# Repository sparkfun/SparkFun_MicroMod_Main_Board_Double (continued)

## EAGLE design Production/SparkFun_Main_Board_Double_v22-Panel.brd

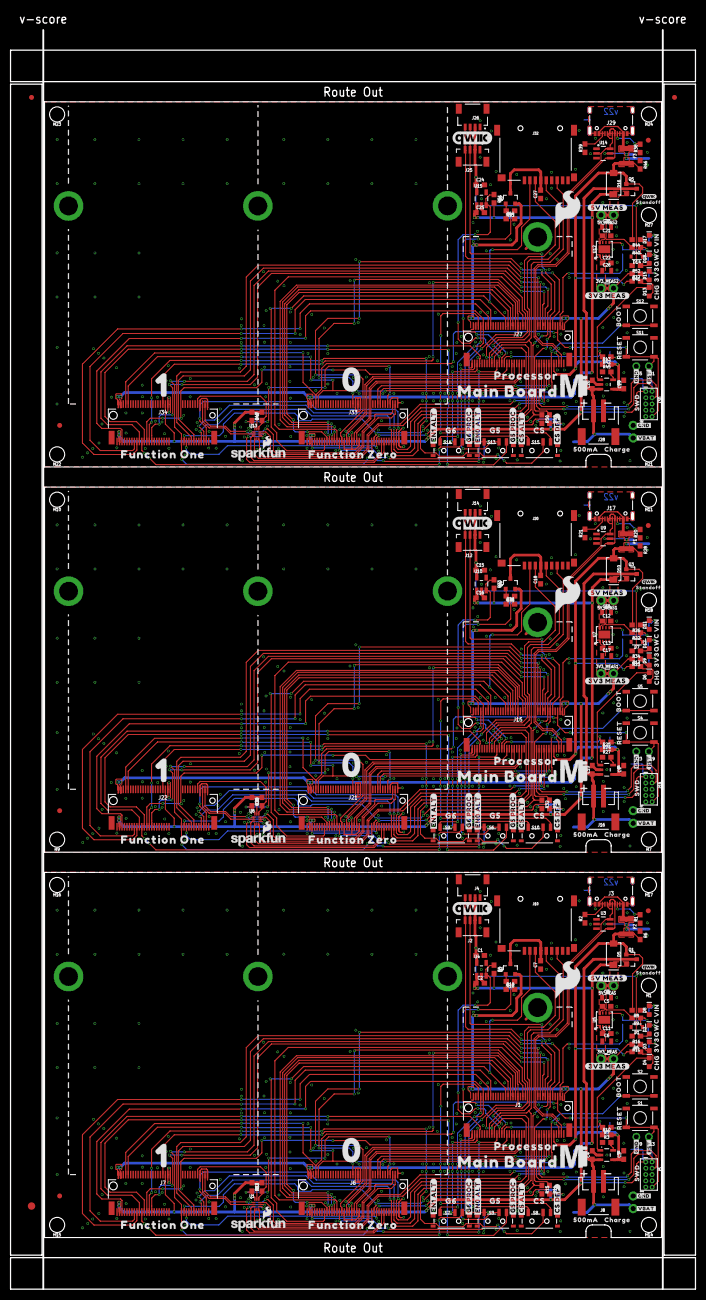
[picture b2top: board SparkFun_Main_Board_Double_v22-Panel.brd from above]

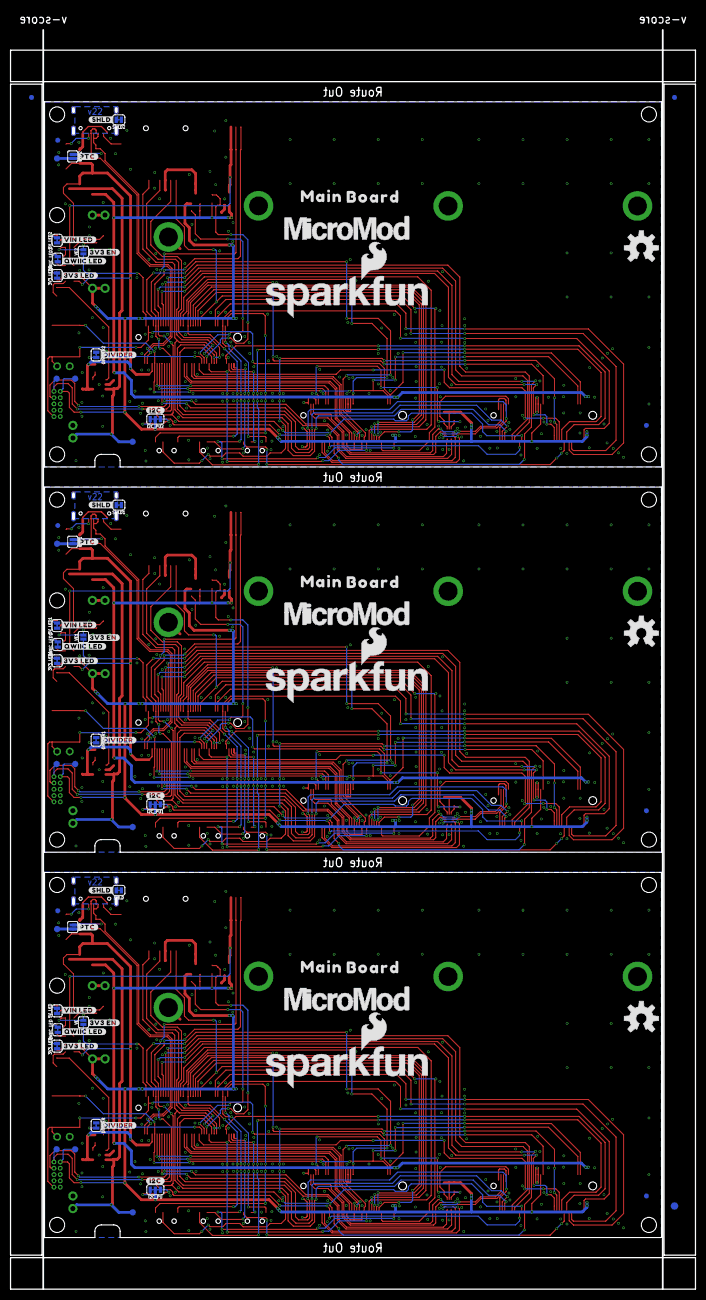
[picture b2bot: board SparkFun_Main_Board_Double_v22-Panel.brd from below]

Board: 2 copper layers, 138.2 x 254.0 mm, 408 parts (84 on the bottom side), 252 nets.

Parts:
3V3_LED, 3V3_LED1, 3V3_LED2, 5V_LED, 5V_LED1, 5V_LED2: JUMPER-SMT_2_NC_TRACE_SILK; SMT-JUMPER_2_NC_TRACE_SILK
3V3_MEAS, 3V3_MEAS1, 3V3_MEAS2, 5V_MEAS, 5V_MEAS1, 5V_MEAS2: JUMPER-COMBO_2_NC_TRACE; COMBO-JUMPER_2_NC_TRACE
BYP, BYP1, BYP2: JUMPER-SMT_2_NO_SILK; SMT-JUMPER_2_NO_SILK
C1, C2, C15, C16, C24, C25: 1.0uF; 0603
C3, C4, C9, C10, C11, C13, C19, C20, C22: 4.7uF; 0603
C5, C12, C21: 0.1uF; 0603
C6, C8, C14, C17, C23, C26: 10uF; 0805
C7, C18, C27: 10uF; 0603
D1, D7, D14: 3.3V; SOD-323
D2, D3, D8, D9, D11, D12, D15, D17, D18: RED; LED-0603
D4, D6, D13: Yellow; LED-0603
D5, D10, D16: 3A/40V/500mV; SMA-DIODE
DIVIDER, DIVIDER1, DIVIDER2: JUMPER-SMT_2_NC_TRACE_SILK; SMT-JUMPER_2_NC_TRACE_SILK
E$1, E$2, E$3, E$4: FIDUCIAL-1X2
E$5, E$6: FIDUCIAL-1.5X3
F1, F2, F3: 6V/2A; 1210
FD1, FD2, FD3, FD4, FD5, FD6, FD7, FD8, FD9, FD10, FD11, FD12: FIDUCIAL1X2; FIDUCIAL-1X2
H1, H7, H9, H10, H11, H14, H15, H16, H17, H18, H21, H22, H23, H24, H27: STAND-OFFTIGHT; STAND-OFF-TIGHT
H2, H3, H4, H5, H6, H8, H12, H13, H19, H20, H25, H26: STAND-OFF-REFLOW-M2.5_2.5MM_TALL; STAND-OFF-REFLOW-M2.5
I2C_PU, I2C_PU1, I2C_PU2: JUMPER-SMT_3_2-NC_TRACE_SILK; SMT-JUMPER_3_2-NC_TRACE_SILK
J1, J15, J27: MICROMOD-2222-C; M.2-CONNECTOR-E
J2, J12, J25: Vertical Qwiic Connector; JST04_1MM_VERT
J3, J17, J29: USB-C-16P-2LAYER-PADS
J4, J14, J26: QWIIC_RIGHT_ANGLE; JST04_1MM_RA
J5, J18, J30: CORTEX_JTAG_DEBUG_MINIMUM_PTH; 2X5-PTH-1.27MM
J6, J7, J21, J22, J33, J34: MICROMOD_FUNCTION_MAIN; M.2-CONNECTOR-E-FUNCTION-STANDARD
J8, J16, J28: JST-2-SMD
J9, J13, J19, J23, J31, J35: 1X01_NO_SILK
J10, J20, J32: MICRO-SD-PUSH-PUSH-EXT-PIN; MICROSD-EXTERNALPIN
J11, J24, J36: 1X02_NO_SILK
LOGO1, LOGO4, LOGO7: QWIIC_LOGO_8MM; QWIIC_8MM
LOGO2, LOGO5, LOGO8: SFE_LOGO_NAME_FLAME.3_INCH; SFE_LOGO_NAME_FLAME_.3
LOGO3, LOGO6, LOGO9: OSHW-LOGOL; OSHW-LOGO-L
Q1, Q3, Q5: 3.1A/30V/105mΩ; SOT23-3
Q2, Q4, Q6: 20V/4.2A/52mΩ/1.4W; SOT23-3
QWIIC_LED, QWIIC_LED1, QWIIC_LED2: JUMPER-SMT_2_NC_TRACE_SILK; SMT-JUMPER_2_NC_TRACE_SILK
R1, R2, R20, R21, R38, R39: 5.1k; 0603
R3, R27, R45: 2.0k; 0603
R4, R9, R12, R13, R19, R22, R29, R30, R33, R36, R40, R47, R48, R51, R54: 100k; 0603
R5, R17, R37: 4.7k; 0603
R6, R7, R24, R28, R42, R46: 10k; 0603
R8, R14, R15, R26, R31, R32, R44, R49, R50: 2.2k; 0603
R10, R25, R43: 20k; 0603
R11, R16, R23, R34, R41, R52: 1k; 0603
R18, R35, R53: 100; 0603
S1, S4, S11: Reset; TACTILE_SWITCH_SMD_5.2MM
S2, S5, S12: BOOT; TACTILE_SWITCH_SMD_5.2MM
S3, S6, S7, S8, S9, S10, S13, S14, S15: SWITCH_SPST_SMD_A
SHLD, SHLD1, SHLD2: JUMPER-SMT_2_NC_TRACE_SILK; SMT-JUMPER_2_NC_TRACE_SILK
TP1, TP2, TP3, TP4, TP5, TP6, TP7, TP8, TP9, TP10, TP11, TP12: TEST-POINT3X5; PAD.03X.05
U1, U8, U13: STG3856QTR; STG3856
U2, U6, U11: MCP73831; SOT23-5
U3, U9, U14: ESD Diode; SOT-23-6
U4, U10, U15: AP7347DQ-33W5-7K-3.3V; SOT25
U5, U7, U12: AP7361C-33; UDFN-8
U$1, U$82, U$128: #3V3_LED#22
U$2, U$81, U$127: #3V3_EN#23
U$3, U$89, U$135: ##RST##8
U$4, U$47, U$93: 3V332533
U$5, U$48, U$94: VIN32532
U$6, U$49, U$95: CHG32531
U$7, U$72, U$118: #SHLD#501
U$8, U$50, U$96: BOOT32541
U$9, U$51, U$97: RESET32540
U$10, U$52, U$98: PROCESSOR525
U$11, U$53, U$99: FUNCTION_ZERO520
U$12, U$54, U$100: FUNCTION_ONE524
U$13, U$58, U$104: MAIN523
U$14, U$55, U$101: MICROMOD_MI_LOGO_1
U$15, U$56, U$102: 0523
U$16, U$57, U$103: 1524
U$17, U$61, U$107: MICROMOD_LOGO_1
U$18, U$59, U$105: BOARD524
U$19, U$77, U$123: G518
U$20, U$65, U$111: #CS_ALT#20
U$21, U$60, U$106: MAIN_BOARD5523
U$22, U$62, U$108: QWIIC_3MM
U$23, U$63, U$109: STANDOFF501
U$24, U$64, U$110: SFE_LOGO_FLAME_.3
U$25, U$80, U$126: SWD6522
U$26, U$74, U$120: #3V3_MEAS#6522
U$27, U$71, U$117: CHARGE501
U$28, U$83, U$129: #QWIIC_LED#22
U$29, U$78, U$124: G6519
U$30, U$73, U$119: #I2C#501
U$31, U$75, U$121: #5V_MEAS#6522
U$32, U$79, U$125: CS17
U$33, U$76, U$122: 500MA6520
U$34, U$66, U$112: #CS_DEF#19
U$35, U$67, U$113: #G5_PROC#21
U$36, U$68, U$114: #G6_PROC#21
U$37, U$69, U$115: #EN0_ALT#21
U$38, U$70, U$116: #EN1_ALT#21
U$39, U$40, U$90, U$91, U$136, U$137: #GND#10
U$41, U$84, U$130: #DIVIDER#23
U$42, U$85, U$131: #VIN_LED#24
U$43, U$86, U$132: QWC18
U$44, U$87, U$133: SFE_LOGO_NAME_FLAME_.1
U$45, U$88, U$134: #PTC#13
U$46, U$92, U$138: #VBAT#9
VE, VE1, VE2: JUMPER-SMT_2_NO_SILK; SMT-JUMPER_2_NO_SILK

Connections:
3.3V: 3V3_MEAS.2, 3V3_MEAS.4, I2C_PU.2, J1.2, J1.74, J5.1, J6.73, J7.36, J7.73, Q2.2, R11.2, R12.2, R13.1, TP2.1, U1.P11
3.3V1: 3V3_MEAS1.2, 3V3_MEAS1.4, I2C_PU1.2, J15.2, J15.74, J18.1, J21.73, J22.36, J22.73, Q4.2, R23.2, R29.2, R30.1, TP5.1, U8.P11
3.3V2: 3V3_MEAS2.2, 3V3_MEAS2.4, I2C_PU2.2, J27.2, J27.74, J30.1, J33.73, J34.36, J34.73, Q6.2, R41.2, R47.2, R48.1, TP9.1, U13.P11
3.3V_EN: J1.4, VE.1
3.3V_EN1: J15.4, VE1.1
3.3V_EN2: J27.4, VE2.1
3.3V_EN_VE: D1.C, R9.1, U5.5, VE.2
3.3V_EN_VE1: D7.C, R22.1, U7.5, VE1.2
3.3V_EN_VE2: D14.C, R40.1, U12.5, VE2.2
3.3V_QWIIC: C1.1, J2.2, J4.2, R16.2, U4.5
3.3V_QWIIC1: C15.1, J12.2, J14.2, R34.2, U10.5
3.3V_QWIIC2: C24.1, J25.2, J26.2, R52.2, U15.5
3V3_MEAS: 3V3_MEAS.1, 3V3_MEAS.3, C6.1, C11.1, U5.1
3V3_MEAS1: 3V3_MEAS1.1, 3V3_MEAS1.3, C13.1, C17.1, U7.1
3V3_MEAS2: 3V3_MEAS2.1, 3V3_MEAS2.3, C22.1, C26.1, U12.1
5V_MEAS: 5V_MEAS.2, 5V_MEAS.4, C5.1, C8.1, R9.2, U5.8
5V_MEAS1: 5V_MEAS1.2, 5V_MEAS1.4, C12.1, C14.1, R22.2, U7.8
5V_MEAS2: 5V_MEAS2.2, 5V_MEAS2.4, C21.1, C23.1, R40.2, U12.8
!BOOT!: J1.11, J6.66, J7.66, S2.3, S2.4
!BOOT!1: J15.11, J21.66, J22.66, S5.3, S5.4
!BOOT!2: J27.11, J33.66, J34.66, S12.3, S12.4
!CS0!-PROCESSOR: J1.55, J6.49
!CS0!-PROCESSOR1: J15.55, J21.49
!CS0!-PROCESSOR2: J27.55, J33.49
!CS1!-PROC-JUMPER: J7.49, S8.2
!CS1!-PROC-JUMPER1: J22.49, S10.2
!CS1!-PROC-JUMPER2: J34.49, S15.2
!CS1!-PROCESSOR: J1.70, S8.1
!CS1!-PROCESSOR1: J15.70, S10.1
!CS1!-PROCESSOR2: J27.70, S15.1
!DFU-FC0!: J6.10, R13.2, U1.P12
!DFU-FC0!1: J21.10, R30.2, U8.P12
!DFU-FC0!2: J33.10, R48.2, U13.P12
!DFU-FC1!: J7.10, R12.1, U1.P10
!DFU-FC1!1: J22.10, R29.1, U8.P10
!DFU-FC1!2: J34.10, R47.1, U13.P10
!RESET!: J1.6, J5.10, J6.68, J7.68, J13.1, S1.3, S1.4
!RESET!1: J15.6, J18.10, J19.1, J21.68, J22.68, S4.3, S4.4
!RESET!2: J27.6, J30.10, J31.1, J33.68, J34.68, S11.3, S11.4
A0-PROCESSOR: J1.34, J6.38
A0-PROCESSOR1: J15.34, J21.38
A0-PROCESSOR2: J27.34, J33.38
A1-PROCESSOR/!CS1!-ALT: J1.38, J7.38, S8.3
A1-PROCESSOR/!CS1!-ALT1: J15.38, J22.38, S10.3
A1-PROCESSOR/!CS1!-ALT2: J27.38, J34.38, S15.3
CTS1-PROCESSOR: J1.15, J6.16
CTS1-PROCESSOR1: J15.15, J21.16
CTS1-PROCESSOR2: J27.15, J33.16
D0-PROCESSOR: J1.10, J6.47
D0-PROCESSOR1: J15.10, J21.47
D0-PROCESSOR2: J27.10, J33.47
D1-PROCESSOR: J1.18, J7.47
D1-PROCESSOR1: J15.18, J22.47
D1-PROCESSOR2: J27.18, J34.47
D+: J1.3, J3.A6, J3.B6, U3.6
D+1: J15.3, J17.A6, J17.B6, U9.6
D+2: J27.3, J29.A6, J29.B6, U14.6
D-: J1.5, J3.A7, J3.B7, U3.4
D-1: J15.5, J17.A7, J17.B7, U9.4
D-2: J27.5, J29.A7, J29.B7, U14.4
G0-PROCESSOR: J1.40, J6.53
G0-PROCESSOR1: J15.40, J21.53
G0-PROCESSOR2: J27.40, J33.53
G1-PROCESSOR: J1.42, J6.55
G1-PROCESSOR1: J15.42, J21.55
G1-PROCESSOR2: J27.42, J33.55
G2-PROCESSOR: J1.44, J6.57
G2-PROCESSOR1: J15.44, J21.57
G2-PROCESSOR2: J27.44, J33.57
G3-PROCESSOR: J1.46, J6.59
G3-PROCESSOR1: J15.46, J21.59
G3-PROCESSOR2: J27.46, J33.59
G4-PROCESSOR/SD_CARD_!CS!: J1.48, J6.61, J10.2
G4-PROCESSOR/SD_CARD_!CS!1: J15.48, J20.2, J21.61
G4-PROCESSOR/SD_CARD_!CS!2: J27.48, J32.2, J33.61
G5-JUMPER: J1.73, S3.2
G5-JUMPER1: J15.73, S6.2
G5-JUMPER2: J27.73, S13.2
G5-PROCESSOR: J7.53, S3.1
G5-PROCESSOR1: J22.53, S6.1
G5-PROCESSOR2: J34.53, S13.1
G6-JUMPER: J1.71, S7.2
G6-JUMPER1: J15.71, S9.2
G6-JUMPER2: J27.71, S14.2
G6-PROCESSOR: J7.55, S7.1
G6-PROCESSOR1: J22.55, S9.1
G6-PROCESSOR2: J34.55, S14.1
G7-PROCESSOR: J1.69, J7.57
G7-PROCESSOR1: J15.69, J22.57
G7-PROCESSOR2: J27.69, J34.57
GND: 3V3_LED.1, 5V_LED.1, C1.2, C2.2, C3.2, C4.2, C5.2, C6.2, C7.1, C8.2, C11.2, D1.A, DIVIDER.1, H2.1, H3.1, H4.1, H8.1, J1.1, J1.7, J1.33, J1.36, J1.39, J1.45, J1.75, J2.1, J3.GND, J3.GND2, J4.1, J5.3, J5.5, J5.9, J6.1, J6.2, J6.8, J6.32, J6.33, J6.34, J6.36, J6.39, J6.45, J6.75, J7.1, J7.2, J7.8, J7.32, J7.33, J7.34, J7.39, J7.45, J7.75, J8.1, J9.1, J10.6, J10.10, J10.11, J10.12, J10.13, J11.1, QWIIC_LED.1, R1.1, R2.1, R3.1, R6.1, R19.2, S1.1, S1.2, S2.1, S2.2, SHLD.1, U1.P5, U2.2, U3.2, U4.2, U5.4, U5.EP
GND1: 3V3_LED1.1, 5V_LED1.1, C9.2, C10.2, C12.2, C13.2, C14.2, C15.2, C16.2, C17.2, C18.1, D7.A, DIVIDER1.1, H5.1, H6.1, H12.1, H13.1, J12.1, J14.1, J15.1, J15.7, J15.33, J15.36, J15.39, J15.45, J15.75, J16.1, J17.GND, J17.GND2, J18.3, J18.5, J18.9, J20.6, J20.10, J20.11, J20.12, J20.13, J21.1, J21.2, J21.8, J21.32, J21.33, J21.34, J21.36, J21.39, J21.45, J21.75, J22.1, J22.2, J22.8, J22.32, J22.33, J22.34, J22.39, J22.45, J22.75, J23.1, J24.1, QWIIC_LED1.1, R20.1, R21.1, R27.1, R28.1, R36.2, S4.1, S4.2, S5.1, S5.2, SHLD1.1, U6.2, U7.4, U7.EP, U8.P5, U9.2, U10.2
GND2: 3V3_LED2.1, 5V_LED2.1, C19.2, C20.2, C21.2, C22.2, C23.2, C24.2, C25.2, C26.2, C27.1, D14.A, DIVIDER2.1, H19.1, H20.1, H25.1, H26.1, J25.1, J26.1, J27.1, J27.7, J27.33, J27.36, J27.39, J27.45, J27.75, J28.1, J29.GND, J29.GND2, J30.3, J30.5, J30.9, J32.6, J32.10, J32.11, J32.12, J32.13, J33.1, J33.2, J33.8, J33.32, J33.33, J33.34, J33.36, J33.39, J33.45, J33.75, J34.1, J34.2, J34.8, J34.32, J34.33, J34.34, J34.39, J34.45, J34.75, J35.1, J36.1, QWIIC_LED2.1, R38.1, R39.1, R45.1, R46.1, R54.2, S11.1, S11.2, S12.1, S12.2, SHLD2.1, U11.2, U12.4, U12.EP, U13.P5, U14.2, U15.2
HOST_D+: J1.35, J6.35
HOST_D+1: J15.35, J21.35
HOST_D+2: J27.35, J33.35
HOST_D-: J1.37, J6.37
HOST_D-1: J15.37, J21.37
HOST_D-2: J27.37, J33.37
I2C_!INT!: J1.16, J6.23, J7.23
I2C_!INT!1: J15.16, J21.23, J22.23
I2C_!INT!2: J27.16, J33.23, J34.23
I2C_SCL: J1.14, J2.4, J4.4, J6.21, J7.21, R15.1
I2C_SCL1: J12.4, J14.4, J15.14, J21.21, J22.21, R32.1
I2C_SCL1-PROCESSOR/QWIIC_EN: J1.53, R4.1, U4.3
I2C_SCL1-PROCESSOR/QWIIC_EN1: J15.53, R33.1, U10.3
I2C_SCL1-PROCESSOR/QWIIC_EN2: J27.53, R51.1, U15.3
I2C_SCL2: J25.4, J26.4, J27.14, J33.21, J34.21, R50.1
I2C_SDA: J1.12, J2.3, J4.3, J6.19, J7.19, R14.1
I2C_SDA1: J12.3, J14.3, J15.12, J21.19, J22.19, R31.1
I2C_SDA1-PROCESSOR/!SD_ENABLE!: J1.51, R18.1
I2C_SDA1-PROCESSOR/!SD_ENABLE!1: J15.51, R35.1
I2C_SDA1-PROCESSOR/!SD_ENABLE!2: J27.51, R53.1
I2C_SDA2: J25.3, J26.3, J27.12, J33.19, J34.19, R49.1
unnamed: D4.A, R5.2
unnamed: 5V_LED.2, D8.C
unnamed: D3.A, R11.1
unnamed: J3.B5, R2.2
unnamed: J3.A5, R1.2
unnamed: R3.2, U2.5
unnamed: DIVIDER.2, R7.1
unnamed: D2.C, QWIIC_LED.2
unnamed: D2.A, R16.1
unnamed: 3V3_LED.2, D3.C
unnamed: I2C_PU.3, R14.2
unnamed: D8.A, R8.1
unnamed: I2C_PU.1, R15.2
unnamed: D4.C, U2.1
unnamed: D6.C, U6.1
unnamed: C7.2, J10.4, Q2.3
unnamed: J17.B5, R21.2
unnamed: Q2.1, R18.2, R19.1
unnamed: J17.A5, R20.2
unnamed: D9.A, R23.1
unnamed: D11.A, R26.1
unnamed: 5V_LED1.2, D11.C
unnamed: 3V3_LED1.2, D9.C
unnamed: I2C_PU1.3, R31.2
unnamed: I2C_PU1.1, R32.2
unnamed: R27.2, U6.5
unnamed: DIVIDER1.2, R24.1
unnamed: D12.C, QWIIC_LED1.2
unnamed: D12.A, R34.1
unnamed: C18.2, J20.4, Q4.3
unnamed: Q4.1, R35.2, R36.1
unnamed: D6.A, R17.2
unnamed: D13.C, U11.1
unnamed: J29.B5, R39.2
unnamed: J29.A5, R38.2
unnamed: D15.A, R41.1
unnamed: D17.A, R44.1
unnamed: 5V_LED2.2, D17.C
unnamed: 3V3_LED2.2, D15.C
unnamed: I2C_PU2.3, R49.2
unnamed: I2C_PU2.1, R50.2
unnamed: R45.2, U11.5
unnamed: DIVIDER2.2, R42.1
unnamed: D18.C, QWIIC_LED2.2
unnamed: D18.A, R52.1
unnamed: C27.2, J32.4, Q6.3
unnamed: Q6.1, R53.2, R54.1
unnamed: D13.A, R37.2
PROCESSOR_CAN-RX: J1.41, J6.43
PROCESSOR_CAN-RX1: J15.41, J21.43
PROCESSOR_CAN-RX2: J27.41, J33.43
PROCESSOR_CAN-TX: J1.43, J6.41
PROCESSOR_CAN-TX1: J15.43, J21.41
PROCESSOR_CAN-TX2: J27.43, J33.41
PWM0-PROCESSOR: J1.32, J6.51
PWM0-PROCESSOR1: J15.32, J21.51
PWM0-PROCESSOR2: J27.32, J33.51
PWM1-PROCESSOR: J1.47, J7.51
PWM1-PROCESSOR1: J15.47, J22.51
PWM1-PROCESSOR2: J27.47, J34.51
RTS1-PROCESSOR: J1.13, J6.18
RTS1-PROCESSOR1: J15.13, J21.18
RTS1-PROCESSOR2: J27.13, J33.18
RX1-DFU_TX-FC0-PLEX: J6.4, U1.P9
RX1-DFU_TX-FC0-PLEX1: J21.4, U8.P9
RX1-DFU_TX-FC0-PLEX2: J33.4, U13.P9
RX1-DFU_TX-FC1-PLEX: J7.4, U1.P8
RX1-DFU_TX-FC1-PLEX1: J22.4, U8.P8
RX1-DFU_TX-FC1-PLEX2: J34.4, U13.P8
RX1-PROCESSOR: J1.19, U1.P6
RX1-PROCESSOR1: J15.19, U8.P6
RX1-PROCESSOR2: J27.19, U13.P6
RX1-PROCESSOR-PLEX: J6.13, U1.P7
RX1-PROCESSOR-PLEX1: J21.13, U8.P7
RX1-PROCESSOR-PLEX2: J33.13, U13.P7
RX2-PROCESSOR: J1.20, J7.13
RX2-PROCESSOR1: J15.20, J22.13
RX2-PROCESSOR2: J27.20, J34.13
SDIO_DATA1/PWR_EN1_ALT: J1.66, J7.71, S7.3
SDIO_DATA1/PWR_EN1_ALT1: J15.66, J22.71, S9.3
SDIO_DATA1/PWR_EN1_ALT2: J27.66, J34.71, S14.3
SDIO_DATA2/PWR_EN0_ALT: J1.68, J6.71, S3.3
SDIO_DATA2/PWR_EN0_ALT1: J15.68, J21.71, S6.3
SDIO_DATA2/PWR_EN0_ALT2: J27.68, J33.71, S13.3
SHLD: J3.SHLD1, J3.SHLD2, J3.SHLD3, J3.SHLD4, SHLD.2
SHLD1: J17.SHLD1, J17.SHLD2, J17.SHLD3, J17.SHLD4, SHLD1.2
SHLD2: J29.SHLD1, J29.SHLD2, J29.SHLD3, J29.SHLD4, SHLD2.2
SPI_PROCESSOR_SCK: J1.57, J6.3, J7.3, J10.5
SPI_PROCESSOR_SCK1: J15.57, J20.5, J21.3, J22.3
SPI_PROCESSOR_SCK2: J27.57, J32.5, J33.3, J34.3
SPI_PROCESSOR_SDI: J1.61, J6.7, J7.7, J10.7
SPI_PROCESSOR_SDI1: J15.61, J20.7, J21.7, J22.7
SPI_PROCESSOR_SDI2: J27.61, J32.7, J33.7, J34.7
SPI_PROCESSOR_SDO: J1.59, J6.5, J7.5, J10.3
SPI_PROCESSOR_SDO1: J15.59, J20.3, J21.5, J22.5
SPI_PROCESSOR_SDO2: J27.59, J32.3, J33.5, J34.5
SPI_SCK1-PROCESSOR: J1.60, J7.61
SPI_SCK1-PROCESSOR1: J15.60, J22.61
SPI_SCK1-PROCESSOR2: J27.60, J34.61
SPI_SDO1-PROCESSOR: J1.62, J7.59
SPI_SDO1-PROCESSOR1: J15.62, J22.59
SPI_SDO1-PROCESSOR2: J27.62, J34.59
SWDCK: J1.21, J5.4
SWDCK1: J15.21, J18.4
SWDCK2: J27.21, J30.4
SWDIO: J1.23, J5.2, TP1.1
SWDIO1: J15.23, J18.2, TP8.1
SWDIO2: J27.23, J30.2, TP12.1
TX1-DFU_RX-FC0-PLEX: J6.6, U1.P1
TX1-DFU_RX-FC0-PLEX1: J21.6, U8.P1
TX1-DFU_RX-FC0-PLEX2: J33.6, U13.P1
TX1-DFU_RX-FC1-PLEX: J7.6, U1.P2
TX1-DFU_RX-FC1-PLEX1: J22.6, U8.P2
TX1-DFU_RX-FC1-PLEX2: J34.6, U13.P2
TX1-PROCESSOR: J1.17, U1.P4
TX1-PROCESSOR1: J15.17, U8.P4
TX1-PROCESSOR2: J27.17, U13.P4
TX1-PROCESSOR-PLEX: J6.15, U1.P3
TX1-PROCESSOR-PLEX1: J21.15, U8.P3
TX1-PROCESSOR-PLEX2: J33.15, U13.P3
TX2-PROCESSOR: J1.22, J7.15
TX2-PROCESSOR1: J15.22, J22.15
TX2-PROCESSOR2: J27.22, J34.15
VCC: 5V_MEAS.1, 5V_MEAS.3, C2.1, D5.C, J6.72, J6.74, J7.72, J7.74, Q1.2, R4.2, U4.1
VCC1: 5V_MEAS1.1, 5V_MEAS1.3, C16.1, D10.C, J21.72, J21.74, J22.72, J22.74, Q3.2, R33.2, U10.1
VCC2: 5V_MEAS2.1, 5V_MEAS2.3, C25.1, D16.C, J33.72, J33.74, J34.72, J34.74, Q5.2, R51.2, U15.1
VIN: BYP.2, C3.1, D5.A, F2.2, J1.9, Q1.1, R5.1, R6.2, R8.2, R10.2, TP4.1, U2.4
VIN1: BYP1.2, C9.1, D10.A, F1.2, J15.9, Q3.1, R17.1, R25.2, R26.2, R28.2, TP7.1, U6.4
VIN2: BYP2.2, C19.1, D16.A, F3.2, J27.9, Q5.1, R37.1, R43.2, R44.2, R46.2, TP11.1, U11.4
VIN/1: J15.49, R24.2, R25.1
VIN/2: J27.49, R42.2, R43.1
VIN/3: J1.49, R7.2, R10.1
V_BATT: C4.1, J8.2, J11.2, Q1.3, TP3.1, U2.3
V_BATT1: C10.1, J16.2, J24.2, Q3.3, TP6.1, U6.3
V_BATT2: C20.1, J28.2, J36.2, Q5.3, TP10.1, U11.3
V_USB: BYP.1, F2.1, J3.VBUS1, J3.VBUS2, U3.5
V_USB1: BYP1.1, F1.1, J17.VBUS1, J17.VBUS2, U9.5
V_USB2: BYP2.1, F3.1, J29.VBUS1, J29.VBUS2, U14.5

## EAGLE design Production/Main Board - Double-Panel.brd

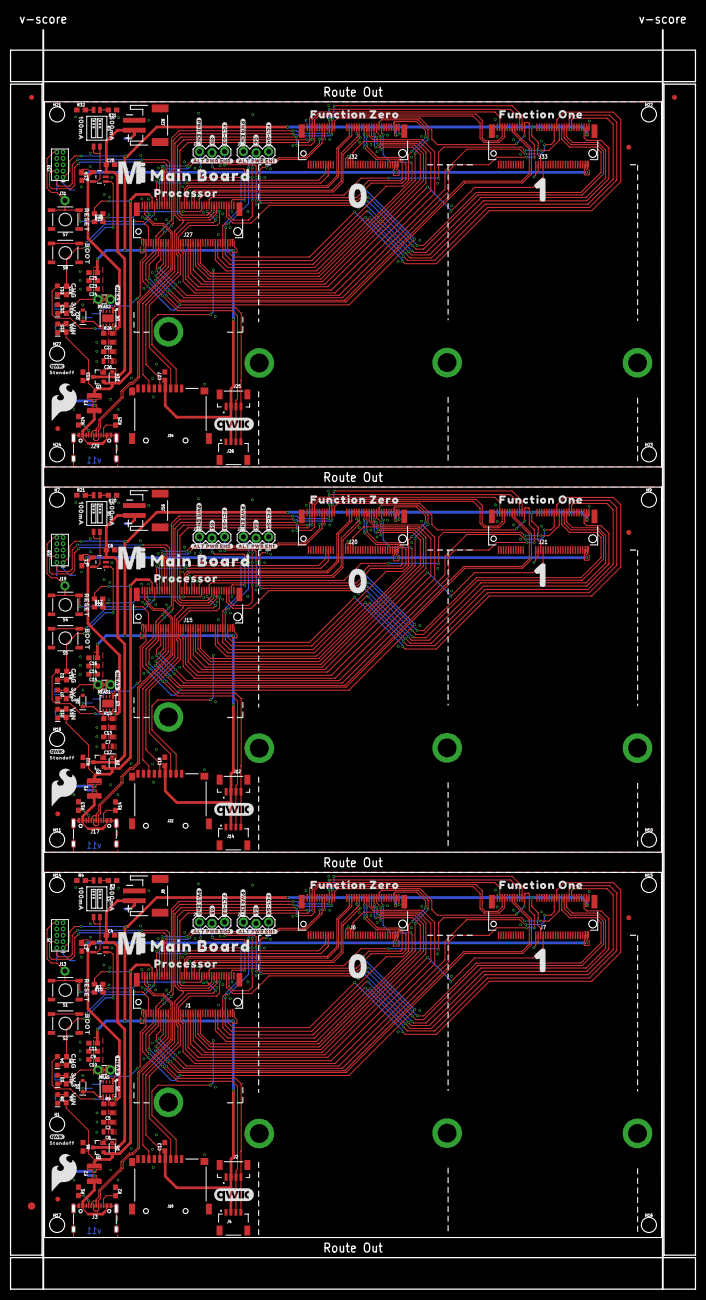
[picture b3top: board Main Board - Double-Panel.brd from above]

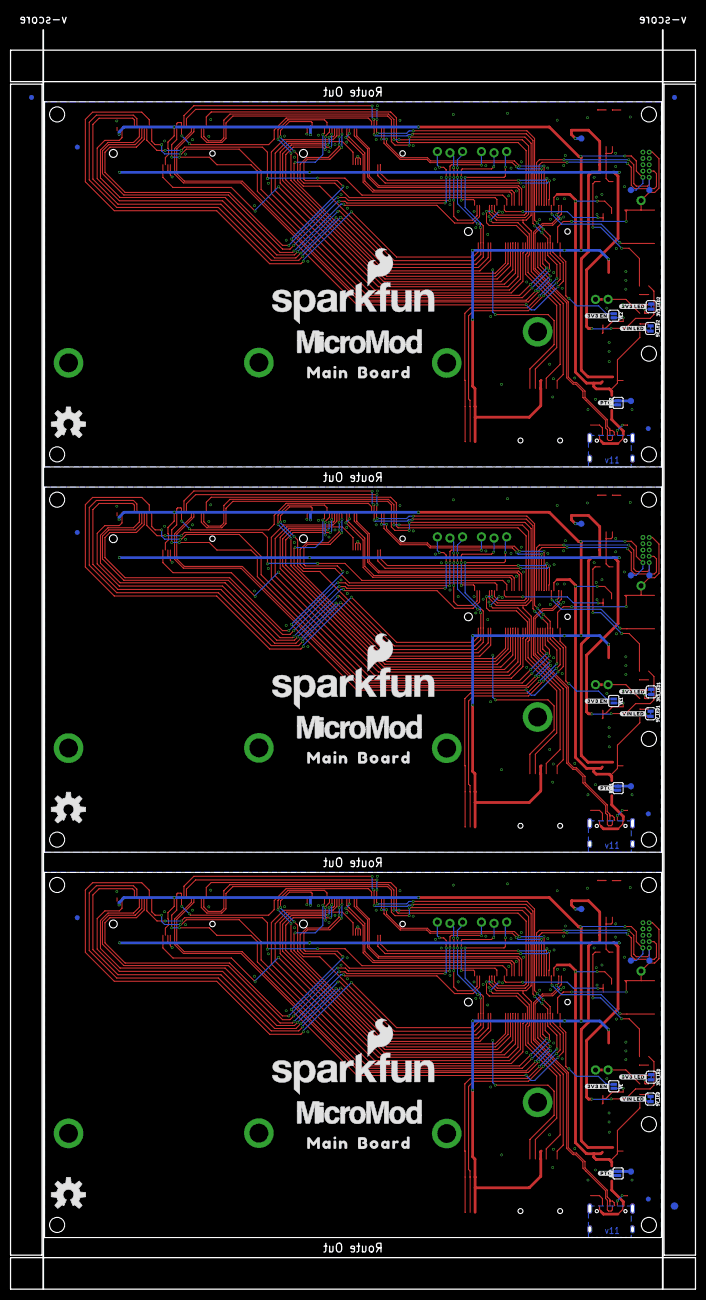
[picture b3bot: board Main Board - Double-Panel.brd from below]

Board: 2 copper layers, 138.2 x 254.0 mm, 312 parts (60 on the bottom side), 195 nets.

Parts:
3V3_LED, 3V3_LED1, 3V3_LED2, 5V_LED, 5V_LED1, 5V_LED2: SMT-JUMPER_2_NC_TRACE_SILK
BYP, BYP1, BYP2: JUMPER-SMT_2_NO_SILK; SMT-JUMPER_2_NO_SILK
C1, C3, C4, C6, C19, C20: 4.7uF; 0603
C2, C7, C11, C16, C21, C25: 0.22uF; 0603
C5, C10, C12, C13, C15, C18, C22, C24, C27: 0.1uF; 0603
C8, C17, C26: 10uF; 0805
C9, C14, C23: 1.0uF; 0603
D1, D6, D12: 3.3V; SOD-323
D2, D4, D11: Yellow; LED-0603
D3, D7, D8, D10, D13, D15: RED; LED-0603
D5, D9, D14: 3A/10V/280mV; SOD-323
E$1, E$2, E$3, E$4: FIDUCIAL-1X2
E$5, E$6: FIDUCIAL-1.5X3
F1, F2, F3: 6V/2A; 1210
FD1, FD2, FD3, FD4, FD5, FD6, FD7, FD8, FD9, FD10, FD11, FD12: FIDUCIAL1X2; FIDUCIAL-1X2
H1, H7, H9, H10, H11, H14, H15, H16, H17, H18, H21, H22, H23, H24, H27: STAND-OFFTIGHT; STAND-OFF-TIGHT
H2, H3, H4, H5, H6, H8, H12, H13, H19, H20, H25, H26: STAND-OFF-REFLOW-M2.5_2.5MM_TALL; STAND-OFF-REFLOW-M2.5
J1, J15, J27: MICROMOD-2222-C; M.2-CONNECTOR-E
J2, J12, J25: Vertical Qwiic Connector; JST04_1MM_VERT
J3, J17, J29: USB-C-16P-2LAYER-PADS
J4, J14, J26: QWIIC_RIGHT_ANGLE; JST04_1MM_RA
J5, J18, J30: CORTEX_JTAG_DEBUG_MINIMUM_PTH; 2X5-PTH-1.27MM
J6, J7, J20, J21, J32, J33: MICROMOD_CARRIER; M.2-CONNECTOR-E-FUNCTION-STANDARD
J8, J16, J28: JST-2-SMD
J9, J11, J23, J24, J35, J36: 1X03_LOCK
J10, J22, J34: MICRO-SD-PUSH-PUSH-EXT-PIN; MICROSD-EXTERNALPIN
J13, J19, J31: 1X01_NO_SILK
LOGO1, LOGO4, LOGO7: QWIIC_LOGO_8MM; QWIIC_8MM
LOGO2, LOGO5, LOGO8: SFE_LOGO_NAME_FLAME.3_INCH; SFE_LOGO_NAME_FLAME_.3
LOGO3, LOGO6, LOGO9: OSHW-LOGOL; OSHW-LOGO-L
MEAS, MEAS1, MEAS2: JUMPER-COMBO_2_NC_TRACE; COMBO-JUMPER_2_NC_TRACE
Q1, Q2, Q3: 3.1A/30V/105mΩ; SOT23-3
R1, R2, R13, R14, R24, R25: 5.1k; 0603
R3, R20, R31: 2.0k; 0603
R4, R6, R7, R17, R21, R22, R28, R32, R33: 10k; 0603
R5, R11, R12, R16, R23, R27: 1k; 0603
R8, R19, R30: 4.7k; 0603
R9, R15, R26: 100k; 0603
R10, R18, R29: 20k; 0603
S1, S4, S7: Reset; TACTILE_SWITCH_SMD_5.2MM
S2, S5, S8: BOOT; TACTILE_SWITCH_SMD_5.2MM
S3, S6, S9: DIP-02-SMD-50MIL; DIPSWITCH-02-50MIL
TP1, TP2, TP3, TP4, TP5, TP6, TP7, TP8, TP9, TP10, TP11, TP12: TEST-POINT3X5; PAD.03X.05
U1, U2, U4: MCP73831; SOT23-5
U3, U5, U6: AP7361C-33; UDFN-8
U$1, U$34, U$67: #3V3_EN#18
U$2, U$35, U$68: #3V3_LED#17
U$3, U$36, U$69: #VIN_LED#16
U$4, U$37, U$70: 3V332533
U$5, U$38, U$71: VIN32532
U$6, U$39, U$72: CHG32531
U$7, U$40, U$73: #PTC#18
U$8, U$41, U$74: BOOT32541
U$9, U$42, U$75: RESET32540
U$10, U$43, U$76: PROCESSOR525
U$11, U$44, U$77: FUNCTION_ZERO520
U$12, U$45, U$78: FUNCTION_ONE524
U$13, U$49, U$82: MAIN523
U$14, U$46, U$79: MICROMOD_MI_LOGO_1
U$15, U$47, U$80: 0523
U$16, U$48, U$81: 1524
U$17, U$54, U$87: MICROMOD_LOGO_1
U$18, U$50, U$83: BOARD524
U$19, U$51, U$84: 100MA6
U$20, U$52, U$85: 500MA101
U$21, U$53, U$86: MAIN_BOARD5523
U$22, U$55, U$88: QWIIC_3MM
U$23, U$56, U$89: STANDOFF501
U$24, U$57, U$90: SFE_LOGO_FLAME_.3
U$25, U$62, U$95: #ALT_PWR_EN0#510
U$26, U$63, U$96: #ALT_PWR_EN1#510
U$27, U$64, U$97: #FC1#G3#518
U$28, U$65, U$98: #FC1#G4#518
U$29, U$58, U$91: #G6#517
U$30, U$59, U$92: #PWR_EN0#517
U$31, U$60, U$93: #PWR_EN1#517
U$32, U$61, U$94: #G5#517
U$33, U$66, U$99: #MEAS#40313513
VE, VE1, VE2: SMT-JUMPER_2_NO_SILK

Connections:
3.3V: C9.1, C10.1, C11.1, C12.1, J1.2, J1.74, J2.2, J4.2, J5.1, J6.73, J7.36, J7.73, J10.4, MEAS.2, MEAS.4, R11.2, TP2.1
3.3V1: C14.1, C15.1, C16.1, C18.1, J12.2, J14.2, J15.2, J15.74, J18.1, J20.73, J21.36, J21.73, J22.4, MEAS1.2, MEAS1.4, R16.2, TP5.1
3.3V2: C23.1, C24.1, C25.1, C27.1, J25.2, J26.2, J27.2, J27.74, J30.1, J32.73, J33.36, J33.73, J34.4, MEAS2.2, MEAS2.4, R27.2, TP9.1
3.3V_EN: J1.4, VE.1
3.3V_EN1: J15.4, VE1.1
3.3V_EN2: J27.4, VE2.1
3.3V_EN_VE: D1.C, R9.1, U5.5, VE.2
3.3V_EN_VE1: D6.C, R15.1, U3.5, VE1.2
3.3V_EN_VE2: D12.C, R26.1, U6.5, VE2.2
!BOOT!: J1.11, S2.3, S2.4
!BOOT!1: J15.11, S5.3, S5.4
!BOOT!2: J27.11, S8.3, S8.4
!CS0!-PROCESSOR: J1.55, J6.49
!CS0!-PROCESSOR1: J15.55, J20.49
!CS0!-PROCESSOR2: J27.55, J32.49
!CS1!-PROCESSOR: J1.70, J7.49
!CS1!-PROCESSOR1: J15.70, J21.49
!CS1!-PROCESSOR2: J27.70, J33.49
!RESET!: J1.6, J5.10, J13.1, S1.3, S1.4
!RESET!1: J15.6, J18.10, J19.1, S4.3, S4.4
!RESET!2: J27.6, J30.10, J31.1, S7.3, S7.4
A0-PROCESSOR: J1.34, J6.38
A0-PROCESSOR1: J15.34, J20.38
A0-PROCESSOR2: J27.34, J32.38
A1-PROCESSOR: J1.38, J7.38
A1-PROCESSOR1: J15.38, J21.38
A1-PROCESSOR2: J27.38, J33.38
CTS1-PROCESSOR: J1.15, J6.16
CTS1-PROCESSOR1: J15.15, J20.16
CTS1-PROCESSOR2: J27.15, J32.16
D0-PROCESSOR: J1.10, J6.47
D0-PROCESSOR1: J15.10, J20.47
D0-PROCESSOR2: J27.10, J32.47
D1-PROCESSOR: J1.18, J7.47
D1-PROCESSOR1: J15.18, J21.47
D1-PROCESSOR2: J27.18, J33.47
D+: J1.3, J3.A6, J3.B6
D+1: J15.3, J17.A6, J17.B6
D+2: J27.3, J29.A6, J29.B6
D-: J1.5, J3.A7, J3.B7
D-1: J15.5, J17.A7, J17.B7
D-2: J27.5, J29.A7, J29.B7
G0-PROCESSOR: J1.40, J6.53
G0-PROCESSOR1: J15.40, J20.53
G0-PROCESSOR2: J27.40, J32.53
G1-PROCESSOR: J1.42, J6.55
G1-PROCESSOR1: J15.42, J20.55
G1-PROCESSOR2: J27.42, J32.55
G2-PROCESSOR: J1.44, J6.57
G2-PROCESSOR1: J15.44, J20.57
G2-PROCESSOR2: J27.44, J32.57
G3-PROCESSOR: J1.46, J6.59
G3-PROCESSOR1: J15.46, J20.59
G3-PROCESSOR2: J27.46, J32.59
G4-PROCESSOR/SD_CARD_!CS!: J1.48, J6.61, J10.2
G4-PROCESSOR/SD_CARD_!CS!1: J15.48, J20.61, J22.2
G4-PROCESSOR/SD_CARD_!CS!2: J27.48, J32.61, J34.2
G5-JUMPER: J1.73, J9.2
G5-JUMPER1: J15.73, J23.2
G5-JUMPER2: J27.73, J35.2
G5-PROCESSOR: J7.53, J9.3
G5-PROCESSOR1: J21.53, J23.3
G5-PROCESSOR2: J33.53, J35.3
G6-JUMPER: J1.71, J11.2
G6-JUMPER1: J15.71, J24.2
G6-JUMPER2: J27.71, J36.2
G6-PROCESSOR: J7.55, J11.3
G6-PROCESSOR1: J21.55, J24.3
G6-PROCESSOR2: J33.55, J36.3
G7-PROCESSOR: J1.69, J7.57
G7-PROCESSOR1: J15.69, J21.57
G7-PROCESSOR2: J27.69, J33.57
G8-PROCESSOR: J1.62, J7.59
G8-PROCESSOR1: J15.62, J21.59
G8-PROCESSOR2: J27.62, J33.59
G9-PROCESSOR: J1.60, J7.61
G9-PROCESSOR1: J15.60, J21.61
G9-PROCESSOR2: J27.60, J33.61
GND: 3V3_LED.1, 5V_LED.1, C2.2, C3.2, C4.2, C5.2, C8.2, C9.2, C10.2, C11.2, C12.2, D1.A, H2.1, H3.1, H4.1, H8.1, J1.1, J1.7, J1.33, J1.36, J1.39, J1.45, J1.75, J2.1, J3.GND, J3.GND2, J4.1, J5.3, J5.5, J5.9, J6.1, J6.32, J6.33, J6.34, J6.36, J6.39, J6.45, J6.75, J7.1, J7.32, J7.33, J7.34, J7.39, J7.45, J7.75, J8.1, J10.6, J10.10, J10.11, J10.12, J10.13, R1.1, R2.1, R3.1, R4.1, R6.1, R7.1, S1.1, S1.2, S2.1, S2.2, U2.2, U5.4, U5.EP
GND1: 3V3_LED1.1, 5V_LED1.1, C1.2, C6.2, C7.2, C13.2, C14.2, C15.2, C16.2, C17.2, C18.2, D6.A, H5.1, H6.1, H12.1, H13.1, J12.1, J14.1, J15.1, J15.7, J15.33, J15.36, J15.39, J15.45, J15.75, J16.1, J17.GND, J17.GND2, J18.3, J18.5, J18.9, J20.1, J20.32, J20.33, J20.34, J20.36, J20.39, J20.45, J20.75, J21.1, J21.32, J21.33, J21.34, J21.39, J21.45, J21.75, J22.6, J22.10, J22.11, J22.12, J22.13, R13.1, R14.1, R17.1, R20.1, R21.1, R22.1, S4.1, S4.2, S5.1, S5.2, U1.2, U3.4, U3.EP
GND2: 3V3_LED2.1, 5V_LED2.1, C19.2, C20.2, C21.2, C22.2, C23.2, C24.2, C25.2, C26.2, C27.2, D12.A, H19.1, H20.1, H25.1, H26.1, J25.1, J26.1, J27.1, J27.7, J27.33, J27.36, J27.39, J27.45, J27.75, J28.1, J29.GND, J29.GND2, J30.3, J30.5, J30.9, J32.1, J32.32, J32.33, J32.34, J32.36, J32.39, J32.45, J32.75, J33.1, J33.32, J33.33, J33.34, J33.39, J33.45, J33.75, J34.6, J34.10, J34.11, J34.12, J34.13, R24.1, R25.1, R28.1, R31.1, R32.1, R33.1, S7.1, S7.2, S8.1, S8.2, U4.2, U6.4, U6.EP
HOST_D+: J1.35, J6.35
HOST_D+1: J15.35, J20.35
HOST_D+2: J27.35, J32.35
HOST_D-: J1.37, J6.37
HOST_D-1: J15.37, J20.37
HOST_D-2: J27.37, J32.37
I2C_!INT!: J1.16, J6.23, J7.23
I2C_!INT!1: J15.16, J20.23, J21.23
I2C_!INT!2: J27.16, J32.23, J33.23
I2C_SCL: J1.14, J2.4, J4.4, J6.21, J7.21
I2C_SCL1: J12.4, J14.4, J15.14, J20.21, J21.21
I2C_SCL2: J25.4, J26.4, J27.14, J32.21, J33.21
I2C_SDA: J1.12, J2.3, J4.3, J6.19, J7.19
I2C_SDA1: J12.3, J14.3, J15.12, J20.19, J21.19
I2C_SDA2: J25.3, J26.3, J27.12, J32.19, J33.19
unnamed: MEAS.1, MEAS.3, U5.1
unnamed: 5V_LED.2, D8.C
unnamed: D3.A, R11.1
unnamed: J3.B5, R2.2
unnamed: J3.A5, R1.2
unnamed: S3.3, S3.4, U2.5
unnamed: BYP.1, F2.1, J3.VBUS1, J3.VBUS2
unnamed: R3.2, S3.1
unnamed: R4.2, S3.2
unnamed: 3V3_LED.2, D3.C
unnamed: D2.C, R12.2
unnamed: D8.A, R8.1
unnamed: R12.1, U1.1
unnamed: D4.C, R5.2
unnamed: R5.1, U2.1
unnamed: J17.B5, R14.2
unnamed: J17.A5, R13.2
unnamed: MEAS1.1, MEAS1.3, U3.1
unnamed: D7.A, R16.1
unnamed: BYP1.1, F1.1, J17.VBUS1, J17.VBUS2
unnamed: D10.A, R19.1
unnamed: 5V_LED1.2, D10.C
unnamed: 3V3_LED1.2, D7.C
unnamed: S6.3, S6.4, U1.5
unnamed: R20.2, S6.1
unnamed: R21.2, S6.2
unnamed: D11.C, R23.2
unnamed: R23.1, U4.1
unnamed: J29.B5, R25.2
unnamed: J29.A5, R24.2
unnamed: MEAS2.1, MEAS2.3, U6.1
unnamed: D13.A, R27.1
unnamed: BYP2.1, F3.1, J29.VBUS1, J29.VBUS2
unnamed: D15.A, R30.1
unnamed: 5V_LED2.2, D15.C
unnamed: 3V3_LED2.2, D13.C
unnamed: S9.3, S9.4, U4.5
unnamed: R31.2, S9.1
unnamed: R32.2, S9.2
PROCESSOR_CAN-RX: J1.41, J6.43
PROCESSOR_CAN-RX1: J15.41, J20.43
PROCESSOR_CAN-RX2: J27.41, J32.43
PROCESSOR_CAN-TX: J1.43, J6.41
PROCESSOR_CAN-TX1: J15.43, J20.41
PROCESSOR_CAN-TX2: J27.43, J32.41
PWM0-PROCESSOR: J1.32, J6.51
PWM0-PROCESSOR1: J15.32, J20.51
PWM0-PROCESSOR2: J27.32, J32.51
PWM1-PROCESSOR: J1.47, J7.51
PWM1-PROCESSOR1: J15.47, J21.51
PWM1-PROCESSOR2: J27.47, J33.51
PWR_EN0: J1.68, J6.71, J9.1
PWR_EN1: J1.66, J7.71, J11.1
PWR_EN2: J15.68, J20.71, J23.1
PWR_EN3: J15.66, J21.71, J24.1
PWR_EN4: J27.68, J32.71, J35.1
PWR_EN5: J27.66, J33.71, J36.1
RTS1-PROCESSOR: J1.13, J6.18
RTS1-PROCESSOR1: J15.13, J20.18
RTS1-PROCESSOR2: J27.13, J32.18
RX1-PROCESSOR: J1.19, J6.13
RX1-PROCESSOR1: J15.19, J20.13
RX1-PROCESSOR2: J27.19, J32.13
RX2-PROCESSOR: J1.20, J7.13
RX2-PROCESSOR1: J15.20, J21.13
RX2-PROCESSOR2: J27.20, J33.13
SPI_PROCESSOR_SCK: J1.57, J6.3, J7.3, J10.5
SPI_PROCESSOR_SCK1: J15.57, J20.3, J21.3, J22.5
SPI_PROCESSOR_SCK2: J27.57, J32.3, J33.3, J34.5
SPI_PROCESSOR_SDI: J1.61, J6.7, J7.7, J10.7
SPI_PROCESSOR_SDI1: J15.61, J20.7, J21.7, J22.7
SPI_PROCESSOR_SDI2: J27.61, J32.7, J33.7, J34.7
SPI_PROCESSOR_SDO: J1.59, J6.5, J7.5, J10.3
SPI_PROCESSOR_SDO1: J15.59, J20.5, J21.5, J22.3
SPI_PROCESSOR_SDO2: J27.59, J32.5, J33.5, J34.3
SWDCK: J1.21, J5.4
SWDCK1: J15.21, J18.4
SWDCK2: J27.21, J30.4
SWDIO: J1.23, J5.2, TP1.1
SWDIO1: J15.23, J18.2, TP8.1
SWDIO2: J27.23, J30.2, TP12.1
TX1-PROCESSOR: J1.17, J6.15
TX1-PROCESSOR1: J15.17, J20.15
TX1-PROCESSOR2: J27.17, J32.15
TX2-PROCESSOR: J1.22, J7.15
TX2-PROCESSOR1: J15.22, J21.15
TX2-PROCESSOR2: J27.22, J33.15
VCC: C2.1, C3.1, C5.1, C8.1, D4.A, D5.C, J6.72, J6.74, J7.72, J7.74, Q1.2, R9.2, U2.4, U5.8
VCC1: C1.1, C7.1, C13.1, C17.1, D2.A, D9.C, J20.72, J20.74, J21.72, J21.74, Q2.2, R15.2, U1.4, U3.8
VCC2: C19.1, C21.1, C22.1, C26.1, D11.A, D14.C, J32.72, J32.74, J33.72, J33.74, Q3.2, R26.2, U4.4, U6.8
VIN: BYP.2, D5.A, F2.2, J1.9, Q1.1, R6.2, R8.2, R10.2, TP4.1
VIN1: BYP1.2, D9.A, F1.2, J15.9, Q2.1, R18.2, R19.2, R22.2, TP7.1
VIN2: BYP2.2, D14.A, F3.2, J27.9, Q3.1, R29.2, R30.2, R33.2, TP11.1
VIN/1: J15.49, R17.2, R18.1
VIN/2: J27.49, R28.2, R29.1
VIN/3: J1.49, R7.2, R10.1
V_BATT: C4.1, J8.2, Q1.3, TP3.1, U2.3
V_BATT1: C6.1, J16.2, Q2.3, TP6.1, U1.3
V_BATT2: C20.1, J28.2, Q3.3, TP10.1, U4.3

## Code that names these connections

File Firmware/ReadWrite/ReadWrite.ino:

/*
  SD Card Read/Write

  This example shows how to read and write data to and from an SD card file
  The circuit:

  SD card attached to SPI bus as follows:

   SD Card   <=> MicroMod Main Board <=> Artemis Processor Board
   -----------------------------------------------------------------
   SD ENABLE <=>  I2C_SDA1-PROCESSOR <=> pin 9
   PICO/SDO  <=>  SPI_PROCESSOR_SDO  <=> pin 38
   POCI/SDI  <=>  SPI_PROCESSOR_SDI  <=> pin 43
   CLK       <=>  SPI_PROCESSOR_CLK  <=> pin 42
   CS        <=>  D1_PROCESSOR       <=> pin 1 (Main Board - Single)
   or ...
   CS        <=>  G4_PROCESSOR       <=> pin 28 (Main Board - Double)

  created   Nov 2010
  by David A. Mellis
  modified 9 Apr 2012
  by Tom Igoe

  This example code is in the public domain.

*/

#include <SPI.h>
#include <SD.h>

//==========ARTEMIS==========
// The microSD Card CS pin is D1 for the MicroMod Main Board - Single and Artemis Processor (D1). Adjust for your processor if necessary.
#define SD_CS_PIN 1
// The microSD Card's CS pin is G4 for the MicroMod Main Board - Double and Artemis Processor (D28). Adjust for your processor if necessary.
//#define SD_CS_PIN 28

File myFile;

void setup() {
  // Open serial communications and wait for port to open:
  Serial.begin(9600);
  while (!Serial) {
    ; // wait for serial port to connect. Needed for native USB port only
  }


  Serial.print("Initializing SD card...");

  if (!SD.begin(SD_CS_PIN)) {
    Serial.println("initialization failed!");
    while (1);
  }
  Serial.println("initialization done.");

  // open the file. note that only one file can be open at a time,
  // so you have to close this one before opening another.
  myFile = SD.open("test.txt", FILE_WRITE);

  // if the file opened okay, write to it:
  if (myFile) {
    Serial.print("Writing to test.txt...");
    myFile.println("testing 1, 2, 3.");
    // close the file:
    myFile.close();
    Serial.println("done.");
  } else {
    // if the file didn't open, print an error:
    Serial.println("error opening test.txt");
  }

  // re-open the file for reading:
  myFile = SD.open("test.txt");
  if (myFile) {
    Serial.println("test.txt:");

    // read from the file until there's nothing else in it:
    while (myFile.available()) {
      Serial.write(myFile.read());
    }
    // close the file:
    myFile.close();
  } else {
    // if the file didn't open, print an error:
    Serial.println("error opening test.txt");
  }
}

void loop() {
  // nothing happens after setup
}

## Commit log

2021-08-17 Initial Commit (post-prototype, pre finalized-for-REDs)
2021-08-31 Adds second standoff for qwiic boards, attaches VIN net to processor connector
    Deletes second page in schematic
2021-08-31 Fixes trace routing
    * Removes
2021-08-31 Adds silk, removes "VIN/VUSB" jumper
2021-08-31 Double routes power enable for ESP32 processor boards
2021-08-31 Rename polygon to VIN to match the trace, approves some overlap errors
2021-09-02 Adds 2 pin dip switch for charge selection, switches diode to PCHN MOSFET to VBAT net
    * Adds better silk
    * Adds charge selection table to schematic
    * Moves standoffs around
2021-09-02 Moved something in the schematic
2021-09-02 Adds qwiic standoff silk
2021-09-02 Replace MOSFET with another one
2021-09-03 Adds 10k pull down to PCHAN MOSFET
2021-09-07 Adds jumpers to route power enable pins to G0/G1 for processors that don't have those nets routed
    * Adds silk to added jumpers
    * Adds PROD-ID to function board connectors
2021-09-08 Adds PTH headers for shunt selectable settings on G0 and G1 for PWR_EN0 and PWR_EN1 respectively
2021-09-08 Revert "Adds PTH headers for shunt selectable settings on G0 and G1 for PWR_EN0 and PWR_EN1 respectively"
    This reverts commit ddf80de5a278d55282677fb1bccc97569ea5aff3.
2021-09-08 Recreates changes from last change but instead moves jumpers to nets G5/G6
2021-09-08 Fixes typo
2021-09-09 Removes old labels
2021-09-09 Moves labels, seeds more vias
2021-09-10 Adds labels to pwr-enable selection headers, moves SD card slightly towards center of board
2021-09-10 ...and again moves SD card slightly upward
2021-09-10 Adds "Meas" silk
2021-09-10 Renames eagle files - panelizes new design
2021-09-10 Adds new panel that is a single column of three.
2021-10-11 Changes power to Function Boards @ VCC to VCC rather than VIN
2021-10-11 Adds two GND vias
2021-10-11 Rolls to v11
2021-10-11 Updates panel
2021-10-22 Replaces schottky diode
2021-11-03 Updates Function board symbol, fixes some text explaining two pin jumper, corrects charging current.
2021-11-10 Create ReadWrite.ino
    Included modified example with a microSD card from the SD Arduino Library
2021-11-11 Updates the design to use the Micromod-function device in the official SFE Eagle Libs
2022-06-22 Changes resistor values on LEDs, updates plexing symbol, increases capacitor value on microSD
    * Adds NC jumper to shield pin on USB-C
2022-06-22 Updates the symbol for the multiplexer and net names
2022-06-22 Double routes chip select and analog one
2022-06-22 Adds default state to plexer, includes new function card symbol with new plexing control pins
2022-06-22 Fixes swapped RX/TX
2022-06-22 Adds pull up resistors to i2c data lines
2022-06-22 Updates cream and stop layers on uart-multiplexer
    * Updates schematic
    * Routes pullup jumper
2022-06-22 Routes airwires
2022-06-22 Routes more airwires
2022-06-28 Updates design with new dip switch
2022-06-29 Large rework in which many of the traces were routed to leave more space between them.
2022-06-29 Routes more air wires, cleans up DRC
2022-06-29 Routes the last of the iar wires
2022-06-29 Flipped the switches around for better labels
2022-06-29 Adds vias, moves traces for ground pour
2022-06-29 Adds silk
2022-06-29 Approves various wire stub errors
2022-06-30 Fixes some vias, deletes value of jumper
2022-06-30 Fixes ground pour in areas throughout, adds vias, updates net positioning and text layout in schematic
    * Increases cap on output of VREG
2022-07-01 Improves routing, snaps many parts to a much more sensible grid, removes some caps on INPUT and OUTPUT of VREG that were not necessary
    * Adds another MEAS Jumper for 5V side
    * Removes selection on charge circuit (500mA now only)
    * Fixes chip select not being double routed corectly
2022-07-01 Many more grid improvements
2022-07-07 Adds ESD protection to USB lines, replaces switches with cheaper more widely available ones
2022-07-08 Adds new VREG, new VREG added to control 3.3V @ Qwiic Connectors, moves i2c pullup jumper (connected to 3v3 not 3v3_Qwiic)
2022-07-11 Adds silk, updates alignment of existing silk that was not replaced, updates landing pads for new mux part
2022-07-11 Updates text in schematic
2022-07-11 Updates device name and removes value from new VREG
2022-07-11 Fixes ESD Diode
2022-07-11 Adds ICs necessary for discrete UART switcher to library
    * Places new parts into "discrete" version of the main board.
2022-07-11 Matches length of D+ and D-
2022-07-11 Adds Gerbers for Main Board (non-discrete)
2022-07-12 Renames gerbers to include version number
2022-07-15 Fixes vias that are intended to be ground to be ground
2022-08-18 Adds a totally different design - designed in Fusion, pushed back here to fix silk
2022-08-18 Changes resistor divider jumper name and qwiic_led jumper name
2022-08-18 Clears overlap DRC errors
2022-08-19 Removes old designs, updates polygons
    * Updates silk
    * Uses VIN as power supply to battery charger
    * Fixes PCH Mosfet
2022-08-19 Fixes airwire
2022-08-23 Renames files
2022-08-23 Adds new production files
2022-08-24 Adds PROD-ID to UART Switcher
2022-08-31 Moves I2C pullups to make space for silk
2022-08-31 Renames board files
2022-08-31 Adds new production panel
2022-09-02 Updates PROD ID of new VREG
2022-10-26 Adds new version of main board double
    * The chip selection switch was not routed correctly on the previous version
2022-10-28 Rotates 2 pin JST connector
2022-10-28 Pushes JST 0.1" further into the board
2022-10-28 Adds notch for lipo battery, moves VBAT test point
2022-10-31 Fixes minor width DRC errors
2022-12-14 Updates input voltage range on the VREG
2023-01-04 Update ReadWrite.ino
    update code comments and notes
2023-01-04 Update MicroMod_Main_Board_Double_Enable_Function_Board.ino.ino
    update comments and notes
2023-01-04 Create ReadWrite_Low_Power.ino
    Add example to toggle microSD card Socket's power for low power applications
2023-01-04 Create MicroMod_Main_Enable_Qwiic_Boards.ino
    Add example to toggle Qwiic Port's voltage regulator for low power
2023-01-04 Update File Name and Path
2023-05-03 Updates function board symbol
